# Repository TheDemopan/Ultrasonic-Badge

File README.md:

# Ultrasonic-Badge
Custom PCB device for detecting distances and beeping when something is too close

Repository contains KiCad PCB files for your own fabrication, as well as the 'main.py' file containing the firmware script that runs continuously on the Raspberry Pi Pico

## Materials

To build your own Ultrasonic Badge you will need (per 1 unit)

- Custom PCB from the included KiCad files
- 1x 12x9mm Buzzer
- 1x LED
- 1x RCWL-1601 Ultrasonic Sensor (You do not want the HC-SR04 since it requires 5v, which is greater than the Pico's 3.3v output)
- 1x Raspberry Pi Pico

Optional
- 1x Battery pack with positive and negative leads, with a toggle switch if you wish.
- 1x Case, see 'case_body_rev.stl'

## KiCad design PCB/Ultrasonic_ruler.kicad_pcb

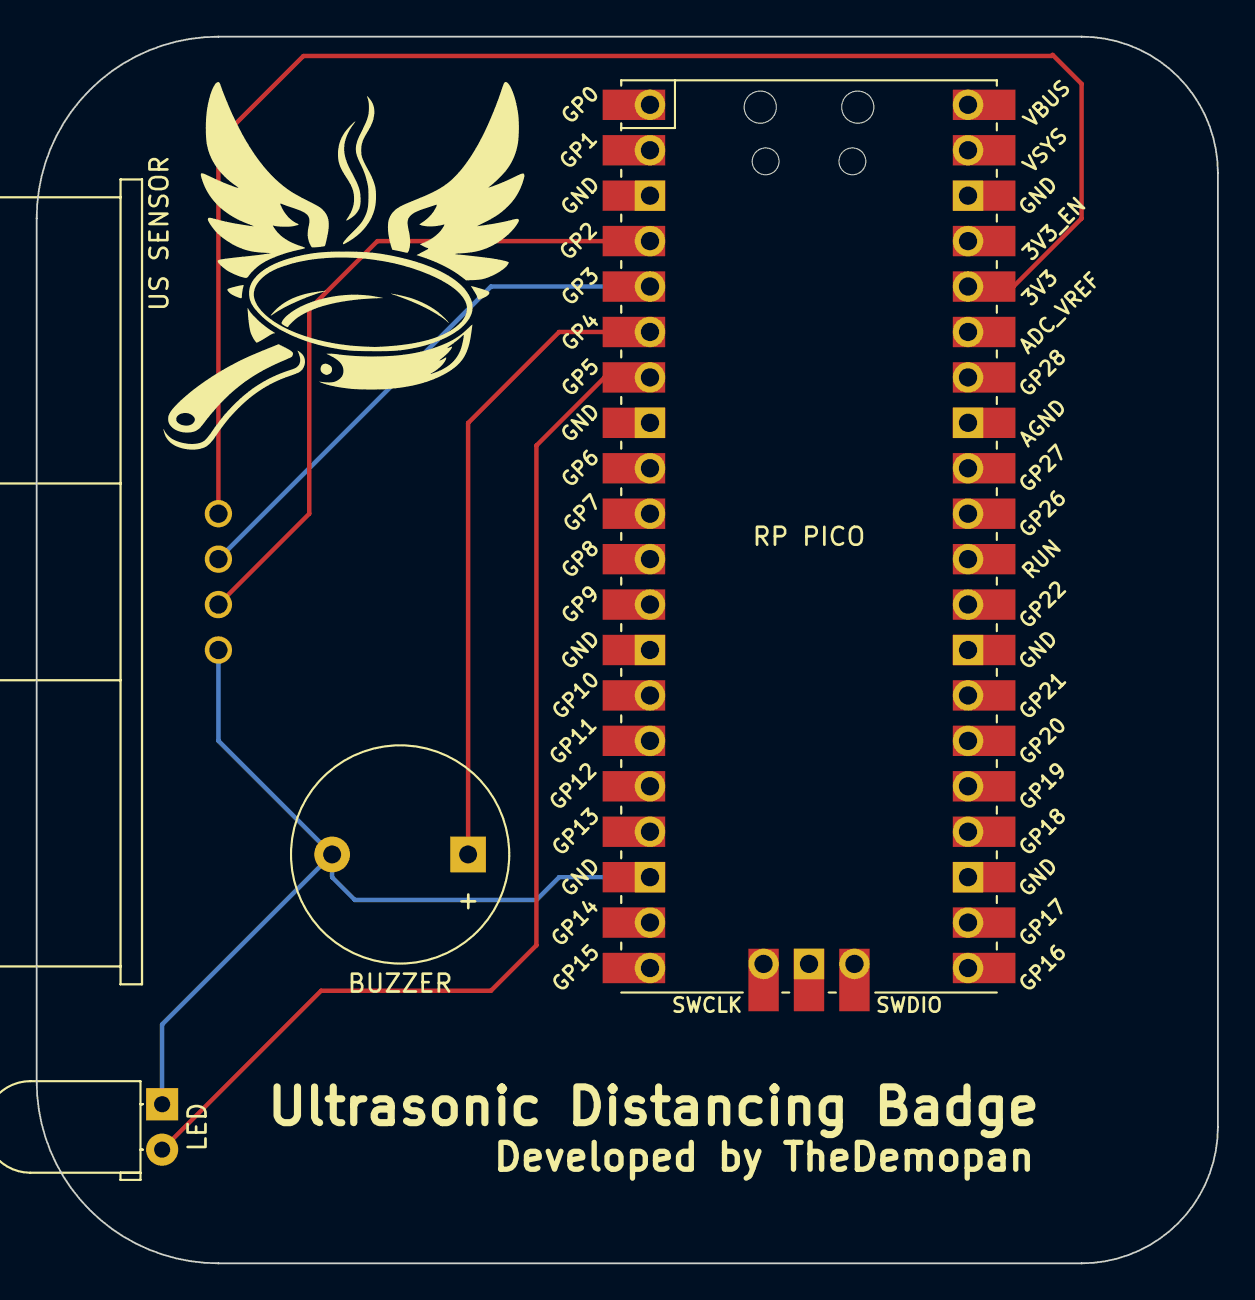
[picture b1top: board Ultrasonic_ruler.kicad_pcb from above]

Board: 2 copper layers, 66.0 x 68.6 mm, 4 parts (0 on the bottom side), 6 nets.

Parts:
BUZZER: Buzzer; Buzzer_12x9.5RM7.6
LED: LED; LED_D5.0mm_Horizontal_O1.27mm_Z3.0mm
RP PICO: RPi_Pico_SMD_TH
US SENSOR: HC-SR04; XCVR_HC-SR04

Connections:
GND: BUZZER.2 (+), LED.1 (K), RP PICO.18, US SENSOR.4 (GND)
unnamed: BUZZER.1 (-), RP PICO.6
unnamed: LED.2 (A), RP PICO.7
unnamed: RP PICO.36, US SENSOR.1 (VCC)
unnamed: RP PICO.4, US SENSOR.3 (ECHO)
unnamed: RP PICO.5, US SENSOR.2 (TRIG)

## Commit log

2023-11-15 Added PCB files and updated readme
